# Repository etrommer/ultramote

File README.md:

# Overview
For a general overview as well as automatically updated documentation, please refer to the [Ultramote website](https://etrommer.github.io/ultramote/)

## Firmware debugging

The firmware debug configuration uses a Black Magic Probe directly as a GDB remote target. It does not require an OpenOCD or pyOCD server. Install `arm-none-eabi-gdb`, build the firmware, and start a direct session with:

```bash
cd firmware
make
arm-none-eabi-gdb build/firmware.elf -x blackmagic.gdb
```

The two Cortex-Debug profiles provide either a flash-and-launch session or an attach-only session.

## Firmware development container

The repository includes a VS Code Dev Container with the pinned STM32CubeMX 6.16.0
Linux package, the STM32CubeWL 1.3.0 firmware package, the GNU Arm Embedded toolchain,
GDB, OpenOCD, and ST-Link tools. Open the repository in VS Code and run **Dev
Containers: Reopen in Container**. The container opens `firmware` as the VS Code
workspace; the repository root is available at `..`.

Build the firmware inside the container:

```bash
make
```

Regenerate CubeMX-managed files from the IOC file without opening a GUI:

```bash
cubemx-generate firmware.ioc
make
```

The image verifies both downloaded archives with SHA-256 checksums. The ST-Link or
Black Magic Probe device must be passed through to the container separately when
debugging; the image does not assume a host device path.

The `pyocd` server type is an alternative only when the connected probe exposes a CMSIS-DAP interface. It is not the transport used by a Black Magic Probe's native GDB interface.

# Firmware
## Remove Lora-E5 readout protection
The Seeedstudio Lora-E5 comes with a preloaded firmware and readout protection enabled. This needs to be disabled before other firmware can be flashed. Run:
```bash
openocd -f interface/stlink.cfg -f target/stm32wlx.cfg
```
then connect to the OpenOCD session from another terminal, using: `nc localhost 4444`. In the telnet session, run:
```
init
reset halt
stm32wlx unlock 0
reset halt
exit
```

# Hardware
## Documentation
Schematics, BoM, Gerber files etc. are generated with the [KiCad command line
interface](https://docs.kicad.org/master/en/cli/cli.html). Change to the `pcb`
directory and run:

```bash
cd pcb
make
```

This generates all documentation in the local subfolder `generated`. `make
docs`, `make fab`, `make step`, `make render` and `make ibom` build single
groups, and `make OUT=<dir>` writes the assets somewhere else. `make` needs
KiCad 10 (`kicad-cli`) and `bsdtar`.

CI runs the same build and publishes the result together with the website
(`.github/workflows/website.yml`). The assets are build output: they are not
committed to the repository, so a local site preview needs

```bash
make -C pcb OUT=website/static/pcb_assets
```

Building the website itself needs Zola 0.22 (`zola --root website build`); 0.23
and later cannot build it, as they replaced the template engine with one that no
longer supports the macros used by the site templates and the `juice` theme.

The interactive BoM needs the
[InteractiveHtmlBom](https://github.com/openscopeproject/InteractiveHtmlBom)
CLI, which must see KiCad's Python bindings. `make` uses one from `PATH` if there
is one, otherwise the copy that ships with the plugin installed through KiCad's
Plugin and Content Manager, so a plugin installation needs no extra setup. Point
`IBOM=` at a CLI from elsewhere (CI installs one from PyPI):

```bash
python3 -m venv --system-site-packages ~/.local/venv/ibom
~/.local/venv/ibom/bin/pip install interactivehtmlbom
make IBOM=~/.local/venv/ibom/bin/generate_interactive_bom
```

If you think that an important piece of documentation is missing, please open an issue.

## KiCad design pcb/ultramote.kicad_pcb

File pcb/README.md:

# Ultramote Hardware
Schematics, BoM, Gerber files etc. are generated using [KiBot](https://github.com/INTI-CMNB/KiBot). To automatically generate documentation, install KiBot [as described here](https://github.com/INTI-CMNB/KiBot#installation).

With kibot installed, change from the root to this directory and run KiBot:
```bash
cd <UltraMote Repo Dir>/pcb
kibot
```
This generates all documentation in the local subfolder `generated`. If you find that anything is missing, please open an issue.

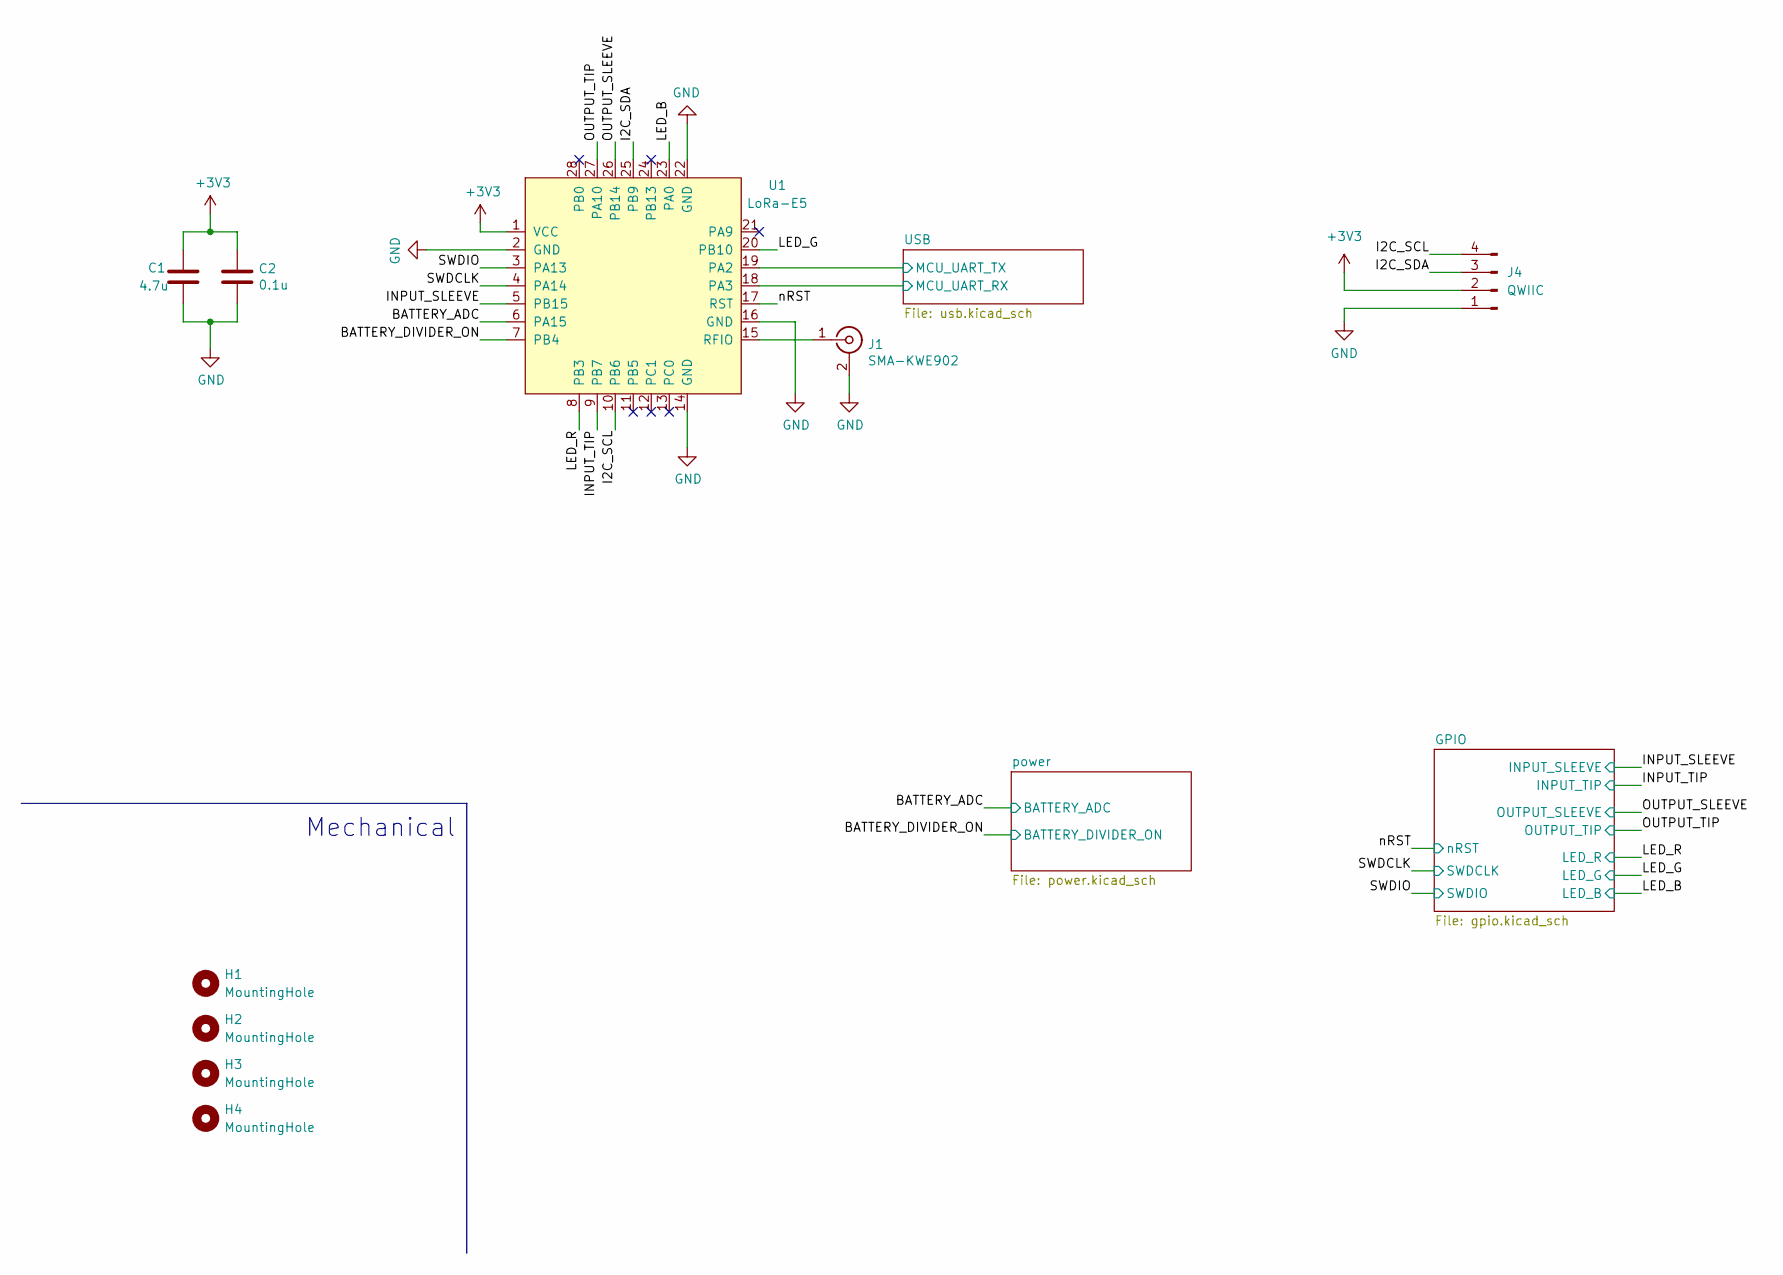
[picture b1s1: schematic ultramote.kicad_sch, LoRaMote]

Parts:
C1: 4.7u; C_0603_1608Metric; Manufacturer Part Number CL10A475MA8NQNC; LCSC Part Number C913907
C2: 0.1u; C_0603_1608Metric; Manufacturer Part Number CL10B104KB8SNNC; LCSC Part Number C570192
H1, H2, H3, H4: MountingHole; MountingHole_2.2mm_M2
J1: SMA-KWE902; Manufacturer Part Number SMA-KE-P903; LCSC Part Number C914554
J4: QWIIC; JST_SH_BM04B-SRSS-TB_1x04-1MP_P1.00mm_Vertical
U1: LoRa-E5

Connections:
+3V3: C1.1, C2.1, J4.2, U1.1 (VCC); also elsewhere on the board
/BATTERY_ADC: U1.6 (PA15); also elsewhere on the board
/BATTERY_DIVIDER_ON: U1.7 (PB4); also elsewhere on the board
/I2C_SCL: J4.4, U1.10 (PB6)
/I2C_SDA: J4.3, U1.25 (PB9)
/INPUT_SLEEVE: U1.5 (PB15); also elsewhere on the board
/INPUT_TIP: U1.9 (PB7); also elsewhere on the board
/LED_B: U1.23 (PA0); also elsewhere on the board
/LED_G: U1.20 (PB10); also elsewhere on the board
/LED_R: U1.8 (PB3); also elsewhere on the board
/OUTPUT_SLEEVE: U1.26 (PB14); also elsewhere on the board
/OUTPUT_TIP: U1.27 (PA10); also elsewhere on the board
/SWDCLK: U1.4 (PA14); also elsewhere on the board
/SWDIO: U1.3 (PA13); also elsewhere on the board
/USB/MCU_UART_RX: U1.18 (PA3); also elsewhere on the board
/USB/MCU_UART_TX: U1.19 (PA2); also elsewhere on the board
/nRST: U1.17 (RST); also elsewhere on the board
GND: C1.2, C2.2, J1.2 (Ext), J4.1, U1.2 (GND), U1.14 (GND), U1.16 (GND), U1.22 (GND); also elsewhere on the board
unnamed: J1.1 (In), U1.15 (RFIO)

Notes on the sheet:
Mechanical

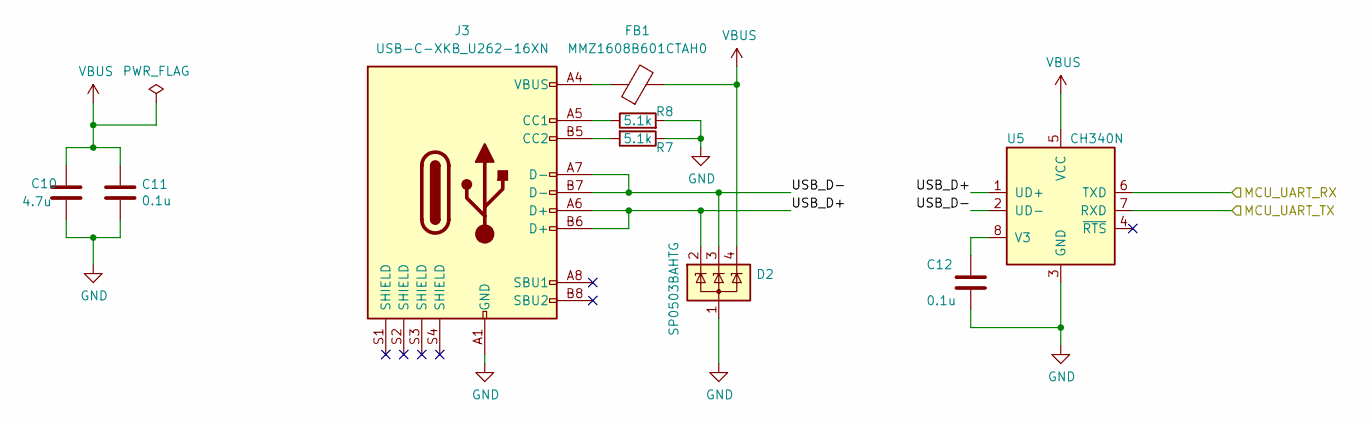
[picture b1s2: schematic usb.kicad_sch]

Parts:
C10: 4.7u; C_0603_1608Metric; Manufacturer Part Number CL10A475MA8NQNC; LCSC Part Number C913907
C11, C12: 0.1u; C_0603_1608Metric; Manufacturer Part Number CL10B104KB8SNNC; LCSC Part Number C570192
D2: SP0503BAHTG; SOT-143; Manufacturer Part Number TPSP0503BAHTG; LCSC Part Number C2682275
FB1: MMZ1608B601CTAH0; C_0603_1608Metric; Manufacturer Part Number MMZ1608B601CTAH0; LCSC Part Number C97120
J3: USB-C-XKB_U262-16XN; USB_C_Receptacle_XKB_U262-16XN-4BVC11; Manufacturer Part Number 918-418K2023S40001; LCSC Part Number C167321
R7, R8: 5.1k; R_0603_1608Metric; Manufacturer Part Number 0603WAF5101T5E; LCSC Part Number C23186
U5: CH340N; SOP-8_3.9x4.9mm_P1.27mm; Manufacturer Part Number CH340N; LCSC Part Number C2977777

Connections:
/USB/MCU_UART_RX: U5.6 (TXD); also elsewhere on the board
/USB/MCU_UART_TX: U5.7 (RXD); also elsewhere on the board
/USB/USB_D+: D2.2 (K), J3.A6 (D+), J3.B6 (D+), U5.1 (UD+)
/USB/USB_D-: D2.3 (K), J3.A7 (D-), J3.B7 (D-), U5.2 (UD-)
GND: C10.2, C11.2, C12.2, D2.1 (A), J3.A1 (GND), J3.A12 (GND), J3.B1 (GND), J3.B12 (GND), R7.2, R8.1, U5.3 (GND); also elsewhere on the board
unnamed: FB1.1, J3.A4 (VBUS), J3.A9 (VBUS), J3.B4 (VBUS), J3.B9 (VBUS)
unnamed: J3.A5 (CC1), R7.1
unnamed: J3.B5 (CC2), R8.2
unnamed: C12.1, U5.8 (V3)
VBUS: C10.1, C11.1, D2.4 (K), FB1.2, U5.5 (VCC); also elsewhere on the board

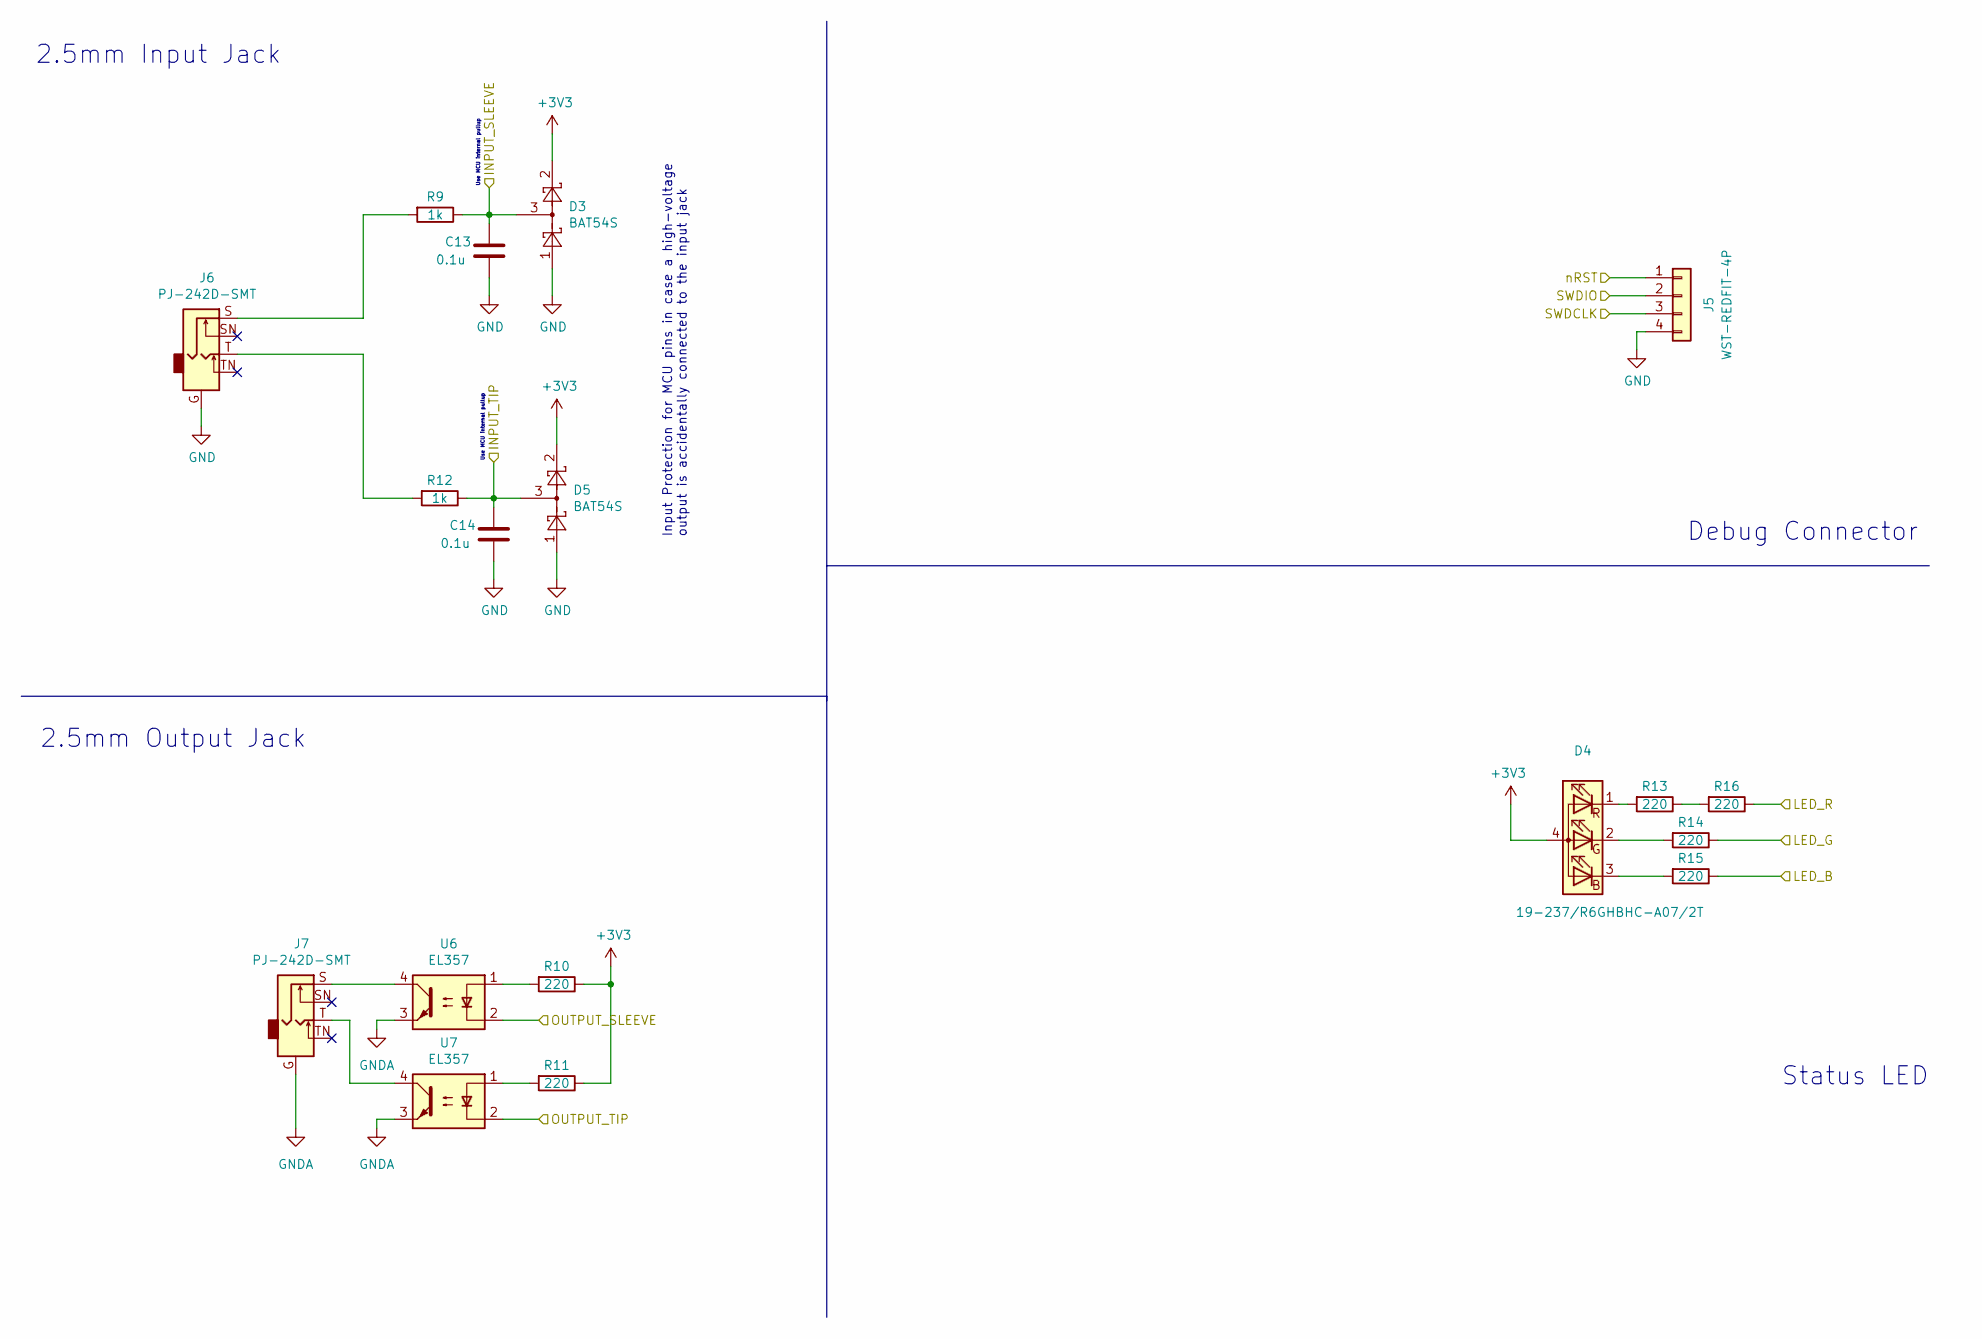
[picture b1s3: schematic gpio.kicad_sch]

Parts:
C13, C14: 0.1u; C_0603_1608Metric; Manufacturer Part Number CL10B104KB8SNNC; LCSC Part Number C570192
D3, D5: BAT54S; SOT-23; Manufacturer Part Number BAT54S; LCSC Part Number C408389
D4: 19-237/R6GHBHC-A07/2T; 19-237-R6GHBHC-A01-2T; Manufacturer Part Number 19-237/R6GHBHC-A07/2T; LCSC Part Number C264511
J5: WST-REDFIT-4P; WR_WST-REDFIT-4P_DEBUG
J6, J7: PJ-242D-SMT; Manufacturer Part Number PJ-242D-SMT; LCSC Part Number C381133
R9, R12: 1k; R_0603_1608Metric; Manufacturer Part Number 0603WAF1001T5E; LCSC Part Number C21190
R10, R11, R13, R14, R15, R16: 220; R_0603_1608Metric; Manufacturer Part Number 0603WAF2200T5E; LCSC Part Number C22962
U6, U7: EL357; EL357N-G; Manufacturer Part Number EL357N(B)(TA)-G; LCSC Part Number C6649

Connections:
+3V3: D3.2, D4.4 (A), D5.2, R10.1, R11.1; also elsewhere on the board
/INPUT_SLEEVE: C13.1, D3.3, R9.1; also elsewhere on the board
/INPUT_TIP: C14.1, D5.3, R12.1; also elsewhere on the board
/LED_B: R15.1; also elsewhere on the board
/LED_G: R14.1; also elsewhere on the board
/LED_R: R16.1; also elsewhere on the board
/OUTPUT_SLEEVE: U6.2; also elsewhere on the board
/OUTPUT_TIP: U7.2; also elsewhere on the board
/SWDCLK: J5.3; also elsewhere on the board
/SWDIO: J5.2; also elsewhere on the board
/nRST: J5.1; also elsewhere on the board
GND: C13.2, C14.2, D3.1, D5.1, J5.4, J6.G; also elsewhere on the board
GNDA: J7.G, U6.3, U7.3
unnamed: D4.3 (BK), R15.2
unnamed: D4.2 (GK), R14.2
unnamed: D4.1 (RK), R13.2
unnamed: J6.S, R9.2
unnamed: J6.T, R12.2
unnamed: J7.S, U6.4
unnamed: J7.T, U7.4
unnamed: R10.2, U6.1
unnamed: R11.2, U7.1
unnamed: R13.1, R16.2

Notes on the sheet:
Status LED
Input Protection for MCU pins in case a high-voltage output is accidentally connected to the input jack
2.5mm Output Jack
2.5mm Input Jack
Use MCU internal pullup
Debug Connector

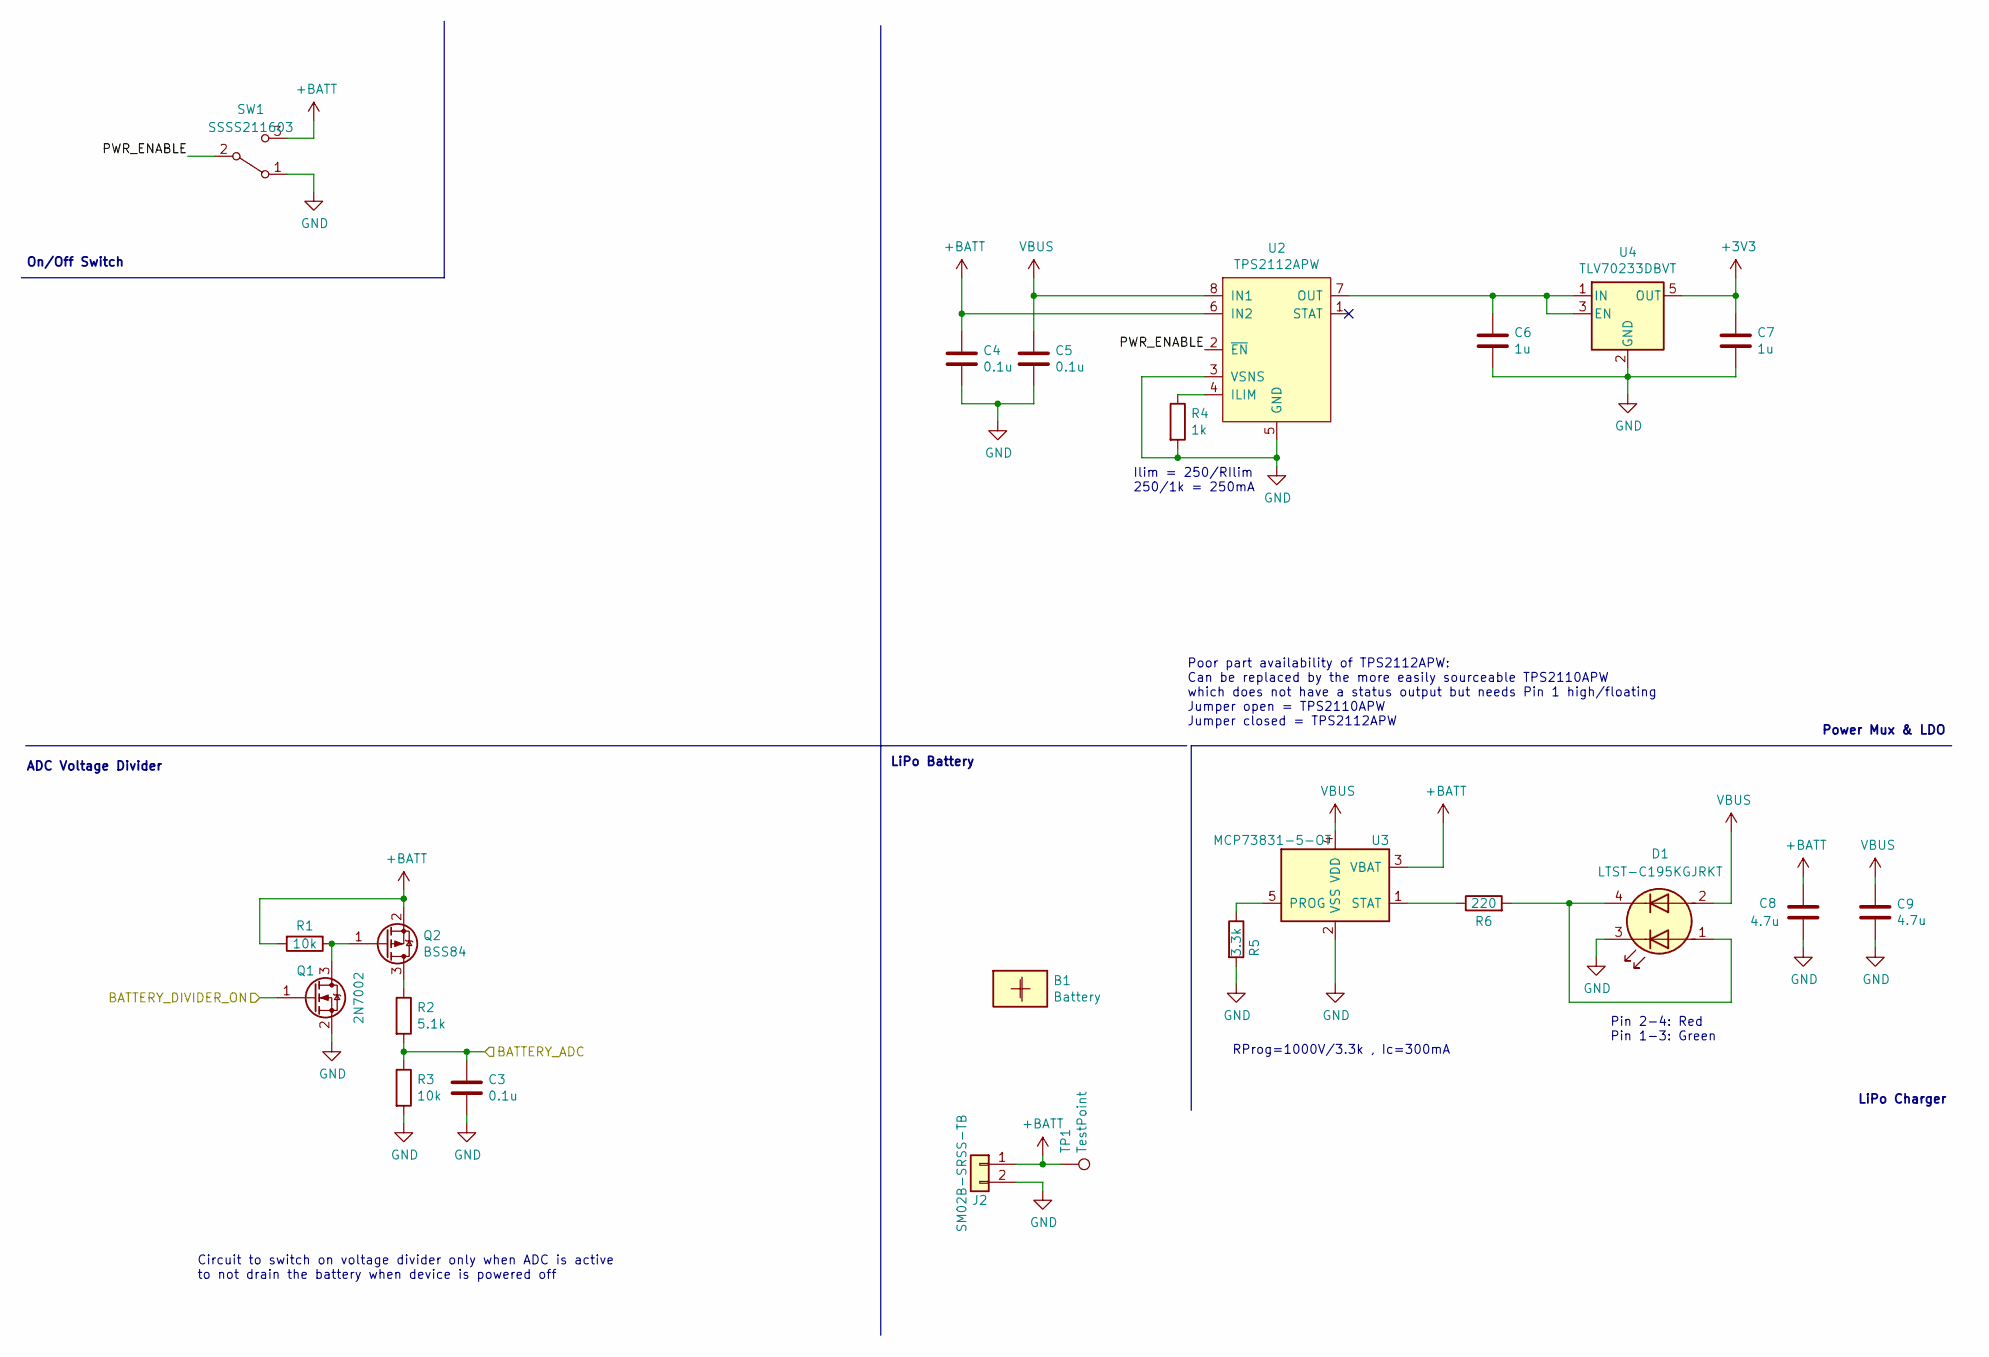
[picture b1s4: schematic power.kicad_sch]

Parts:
B1: Battery; lipo403030_300mah
C3, C4, C5: 0.1u; C_0603_1608Metric; Manufacturer Part Number CL10B104KB8SNNC; LCSC Part Number C570192
C6, C7: 1u; C_0603_1608Metric; Manufacturer Part Number CL10B105KA8NNNC; LCSC Part Number C29936
C8, C9: 4.7u; C_0603_1608Metric; Manufacturer Part Number CL10A475MA8NQNC; LCSC Part Number C913907
D1: LTST-C195KGJRKT; Manufacturer Part Number LTST-C195KGJRKT; LCSC Part Number C125104
J2: SM02B-SRSS-TB; JST_SH_SM02B-SRSS-TB_1x02-1MP_P1.00mm_Horizontal; Manufacturer Part Number S2B-PH-SM4-TB(LF)(SN); LCSC Part Number C160402
Q1: 2N7002; SOT-23; Manufacturer Part Number 2N7002; LCSC Part Number C916396
Q2: BSS84; SOT-23; Manufacturer Part Number BSS84A-TP; LCSC Part Number C668883
R1, R3: 10k; R_0603_1608Metric; Manufacturer Part Number 0603WAF1002T5E; LCSC Part Number C25804
R2: 5.1k; R_0603_1608Metric; Manufacturer Part Number 0603WAF5101T5E; LCSC Part Number C23186
R4: 1k; R_0603_1608Metric; Manufacturer Part Number 0603WAF1001T5E; LCSC Part Number C21190
R5: 3.3k; R_0603_1608Metric; Manufacturer Part Number 0603WAF3301T5E; LCSC Part Number C22978
R6: 220; R_0603_1608Metric; Manufacturer Part Number 0603WAF2200T5E; LCSC Part Number C22962
SW1: SSSS211603; Manufacturer Part Number SSSS211603; LCSC Part Number C125040
TP1: TestPoint; TestPoint_Pad_1.0x1.0mm
U2: TPS2112APW; TSSOP-8_4.4x3mm_P0.65mm; Manufacturer Part Number TPS2112APW; LCSC Part Number C1524008
U3: MCP73831-5-OT; SOT-23-5; Manufacturer Part Number MCP73831T-2ACI/OT; LCSC Part Number C424093
U4: TLV70233DBVT; SOT-23-5; Manufacturer Part Number TLV70233DBVT; LCSC Part Number C110287

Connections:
+3V3: C7.1, U4.5 (OUT); also elsewhere on the board
+BATT: C4.1, C8.1, J2.1, Q2.2 (S), R1.2, SW1.3 (C), TP1.1, U2.6 (IN2), U3.3 (VBAT)
/BATTERY_ADC: C3.1, R2.2, R3.1; also elsewhere on the board
/BATTERY_DIVIDER_ON: Q1.1 (G); also elsewhere on the board
/power/PWR_ENABLE: SW1.2 (B), U2.2 (~EN)
GND: C3.2, C4.2, C5.2, C6.2, C7.2, C8.2, C9.2, D1.3 (K1), J2.2, Q1.2 (S), R3.2, R4.2, R5.2, SW1.1 (A), U2.3 (VSNS), U2.5 (GND), U3.2 (VSS), U4.2 (GND); also elsewhere on the board
unnamed: D1.1 (A1), D1.4 (K2), R6.2
unnamed: Q1.3 (D), Q2.1 (G), R1.1
unnamed: Q2.3 (D), R2.1
unnamed: R4.1, U2.4 (ILIM)
unnamed: C6.1, U2.7 (OUT), U4.1 (IN), U4.3 (EN)
unnamed: R5.1, U3.5 (PROG)
unnamed: R6.1, U3.1 (STAT)
VBUS: C5.1, C9.1, D1.2 (A2), U2.8 (IN1), U3.4 (VDD); also elsewhere on the board

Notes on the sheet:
Poor part availability of TPS2112APW: Can be replaced by the more easily sourceable TPS2110APW which does not have a status output but needs Pin 1 high/floating Jumper open = TPS2110APW Jumper closed = TPS2112APW
LiPo Charger
ADC Voltage Divider
Pin 2-4: Red Pin 1-3: Green
Circuit to switch on voltage divider only when ADC is active to not drain the battery when device is powered off
Ilim = 250/RIlim 250/1k = 250mA
RProg=1000V/3.3k , Ic=300mA
Power Mux & LDO
On/Off Switch
LiPo Battery

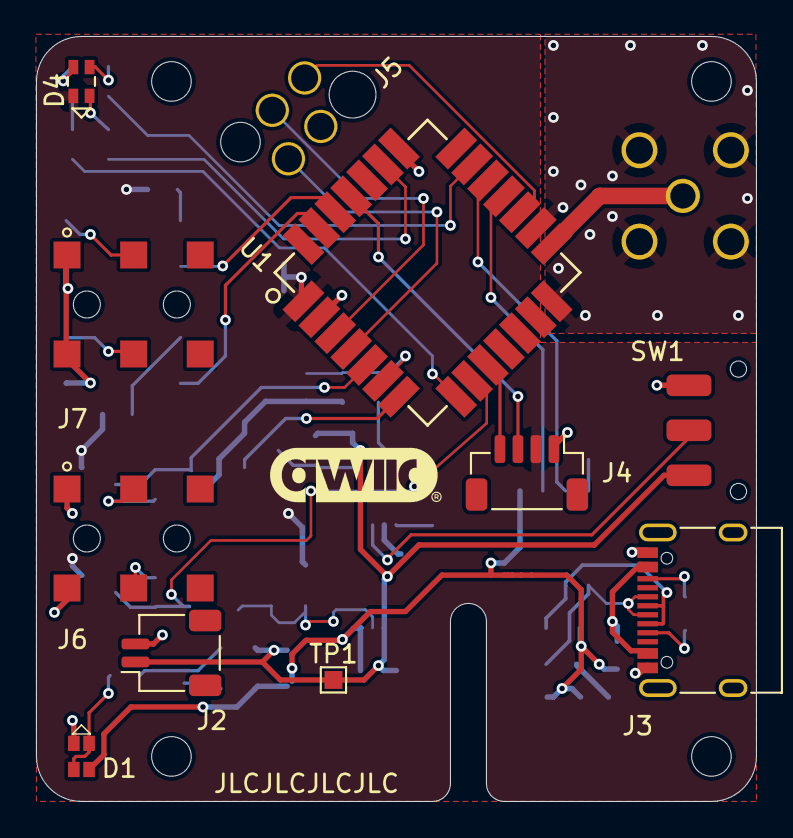
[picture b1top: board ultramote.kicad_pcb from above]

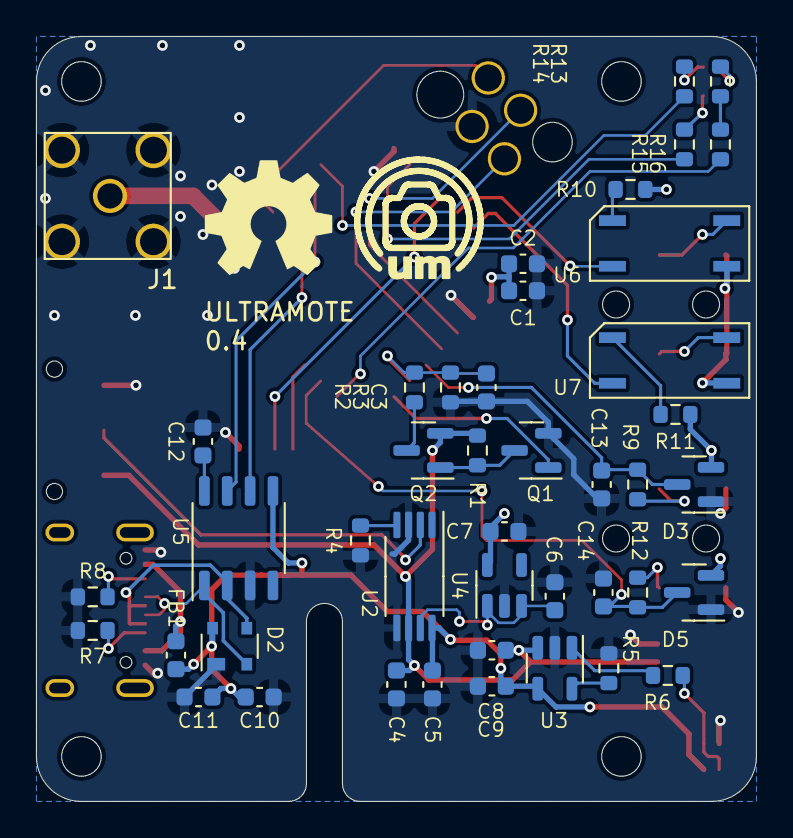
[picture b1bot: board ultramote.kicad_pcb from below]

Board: 2 copper layers, 40.0 x 42.5 mm, 59 parts (43 on the bottom side), 46 nets.

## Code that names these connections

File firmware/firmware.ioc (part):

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Mcu.Name=STM32WLE5JCIx
Mcu.Package=UFBGA73
Mcu.UserName=STM32WLE5JCIx
PA0.GPIOParameters=GPIO_Label
PA0.GPIO_Label=LED_B
PA0.Signal=S_TIM2_CH1
PA10.GPIOParameters=PinState,GPIO_PuPd,GPIO_Label
PA10.GPIO_Label=OUTPUT_TIP
PA10.GPIO_PuPd=GPIO_PULLUP
PA10.PinState=GPIO_PIN_SET
PA10.Signal=GPIO_Output
PA13.Mode=Serial_Wire
PA13.Signal=DEBUG_JTMS-SWDIO
PA14.Mode=Serial_Wire
PA14.Signal=DEBUG_JTCK-SWCLK
PA15.Mode=IN11
PA15.Signal=ADC_IN11
PA2.Mode=Asynchronous
PA2.Signal=USART2_TX
PA3.Mode=Asynchronous
PA3.Signal=USART2_RX
PB0-VDD_TCXO.Mode=HSE-TCXO
PB0-VDD_TCXO.Signal=VDDTCXO
PB10.GPIOParameters=GPIO_Label
PB10.GPIO_Label=LED_G
PB10.Signal=S_TIM2_CH3
PB14.GPIOParameters=PinState,GPIO_Label
PB14.GPIO_Label=OUTPUT_SLEEVE
PB14.PinState=GPIO_PIN_SET
PB14.Signal=GPIO_Output
PB15.GPIOParameters=GPIO_PuPd,GPIO_Label
PB15.GPIO_Label=INPUT_SLEEVE
PB15.GPIO_PuPd=GPIO_PULLUP
PB15.Signal=GPIO_Input
PB3.GPIOParameters=GPIO_Label
PB3.GPIO_Label=LED_R
PB3.Signal=S_TIM2_CH2
PB4.GPIOParameters=GPIO_Label
PB4.GPIO_Label=BATTERY_DIVIDER_ON
PB4.Signal=GPIO_Output
PB6.Mode=I2C
PB6.Signal=I2C1_SCL
PB7.GPIOParameters=GPIO_PuPd,GPIO_Label
PB7.GPIO_Label=INPUT_TIP
PB7.GPIO_PuPd=GPIO_PULLUP
PB7.Signal=GPIO_Input
PB9.Mode=I2C
PB9.Signal=I2C1_SDA
PC14-OSC32_IN.Mode=LSE-External-Oscillator
PC14-OSC32_IN.Signal=RCC_OSC32_IN
PC15-OSC32_OUT.Mode=LSE-External-Oscillator
PC15-OSC32_OUT.Signal=RCC_OSC32_OUT
RCC.HSE_VALUE=8000000
RCC.SYSCLKFreq_VALUE=48000000
board=custom

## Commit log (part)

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2023-02-02 Create LICENSE
2023-02-02 Add README
2023-02-02 Fix ERC warnings
2023-02-02 Fix DRC warnings
2023-02-11 Fix Debug connector registration hole diameter
    - closes #1
2023-02-11 Add datasheet links
2023-02-11 Add Mounting Holes as schematic symbol
2023-02-11 Update footprint library paths
2023-02-11 Remove battery footprint from PCB export
2023-02-11 Add KiBot config
2023-02-11 Generate documentation using Github Actions
2023-02-11 Website initial commit
2023-02-11 Push CI output to website branch
2023-02-11 CI: Update documentation
2023-02-11 Add CI outputs to website
2023-02-11 Add name to website CI run
2023-02-11 Add Favicon
2023-02-11 Restructure index page
2023-02-12 Firmware initial commit
2023-02-12 Minor change in logo
2023-02-12 Add logo to PCB backside
    - closes #3
2023-02-12 Stash and change branch for pushing of Docs
2023-02-13 Deploy etrommer/ultramote to etrommer/ultramote:gh-pages
2023-05-21 Migrate project to KiCad v7
2023-05-21 Fix USB-C 3D model paths
2023-05-21 Fix various 3D models
2023-06-19 Route Output jack through separate ground
2023-06-30 Add Firmware gitignore
2023-06-30 Regenerate Firmware for Rev 3.0 hardware
2023-06-30 Add KiBot output folder to gitignore
2023-07-01 Vanity link to my personal website
2023-07-01 Use logo from PNG
2023-07-01 Revert "Add Firmware gitignore"
    This reverts commit 95a6587d466fa3f0f3f431ca9426635eba17a3f1.
2023-07-01 Add option to manually trigger KiCAD CI run
2023-07-01 Update product page
2023-07-01 Improve LED controller comments
2023-07-01 Update index page greeting
2023-07-02 Fix bug in trigger integrator
2023-07-04 Add fast blink pattern to LED controller
2023-07-04 Increase LoRa frequency, ouput power and spreading factor
2023-07-07 Move App to separate file
    move application code to its own file from main.c because I don't trust
    the HAL code generator not to never overwrite it.
2023-07-07 Reduce LoRa radio air time
2023-07-07 Make battery monitor state machine more consistent
2023-07-07 Add Logging
2023-07-07 Fix inverted channels in trigger
2023-07-07 Minor refactor in radio setup
2023-07-07 Minor refactor in LED controller
2023-07-16 Fix Pin Assignment for Output jack
    closes #4
2023-07-16 Add QWIIC connector
    closes #5
2023-07-16 Update website
2025-09-28 Update to KiCAD v8
2025-12-20 Regenerate sources
2025-12-20 Add battery percentage gauge
2025-12-20 Save PCB with latest KiCAD
